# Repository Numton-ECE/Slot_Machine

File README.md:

Analog Slot Machine – 3-Digit Random Number Generator
=====================================================

This project is a fully discrete, CMOS-based 3-digit “slot machine” random number
generator designed in KiCad. A transistor noise source, analog amplification, and a
comparator generate a pseudo-random clock that drives three CD4026 decade counters and
7-segment LED displays. There is no microcontroller involved.

In normal use:
- A 2N3904 transistor is biased so it produces broadband electronic noise.
- An LM358 dual op-amp amplifies that noise and also creates a mid-supply reference (V_REF).
- An LM393 comparator compares the noisy signal to V_REF and outputs a pseudo-random
  digital clock (CLK).
- CD4013 flip-flops and a CD4081 AND gate handle the RUN state and decide when CLK is
  allowed through.
- Three CD4026 counters drive three 7-segment LED displays (e.g. 5161AS), forming a
  3-digit readout.
- When you hold the RUN pushbutton, the digits “spin”; when you release it, the
  current 3-digit number is frozen on the display.
- The whole circuit runs from a single 9 V battery (PP3).

Hardware Architecture
---------------------

1) Power and Decoupling
- Input is a 9 V battery, with VDD and GND as the main rails.
- Each IC has a 100 nF ceramic capacitor close to its power pins to keep the supply
  clean at high frequencies.
- Electrolytic capacitors on the 9 V rail provide bulk smoothing and help with
  startup and transients.
- This keeps both the analog and digital blocks stable and less sensitive to noise.

2) Noise and Clock Generation
- A 2N3904 NPN transistor is biased in a regime where it naturally produces broadband
  electronic noise. High-value resistors and a small capacitor shape this noise a bit.
- The LM358 op-amp does two jobs:
  - One channel generates V_REF, roughly at mid-supply.
  - The other channel amplifies and band-limits the noise so the comparator sees a
    clean, usable signal.
- The LM393 comparator compares the amplified noise to V_REF:
  - Whenever the noise crosses the reference, the comparator output toggles.
  - This produces a jittery, pseudo-random digital clock signal (CLK), which becomes
    the timing source for the counters.

3) Run / Sync Control and Clock Gating
- A CD4013 dual D-type flip-flop stores the RUN state and any related control bits.
- A dual-pole momentary RUN pushbutton, along with a few diodes and resistors,
  generates clean set/reset and edge-detect pulses so the flip-flop behaves nicely.
- A CD4081 quad 2-input AND gate combines:
  - The random clock (CLK),
  - The RUN state,
  - And any extra gating signals used per digit.
- When RUN is active, CLK passes through the AND gates and reaches the CD4026 counters.
- When RUN is inactive, the clock path is cut off and the counters simply hold their
  last values.
- An SPDT switch is available to select between different modes (for example,
  changing how reset or test behavior works), depending on how you choose to wire it.

4) Counters and Display
- Three CD4026 decade counters are used, one for each decimal digit:
  - Each counter receives a gated clock input from the CD4081, plus reset and control
    wiring for predictable startup.
  - CD4026 devices include built-in 7-segment decoding, so no extra decoder IC is needed.
- Three 7-segment LED displays (such as 5161AS) are driven directly from the CD4026
  outputs through current-limiting resistors (about 2.2 kΩ per segment).
- Together they form a simple 3-digit decimal display:
  - While you hold RUN, the digits advance quickly and look like spinning reels.
  - When you release RUN, the clock stops and the last 3-digit number stays on the
    display until the next run.

Usage
-----

- Open the KiCad project to inspect the schematic and PCB layout.
- If you want a physical board, generate Gerber and drill files from the KiCad PCB
  and send them to a PCB manufacturer.
- Assemble the board starting with resistors and capacitors, then sockets and
  connectors, and finally the ICs and displays.
- After soldering, check that the power rails are correct and there are no shorts
  between VDD and GND.
- Connect a 9 V battery.
- Press and hold the RUN button: the digits should spin rapidly.
- Release RUN: a random 3-digit number should remain displayed.

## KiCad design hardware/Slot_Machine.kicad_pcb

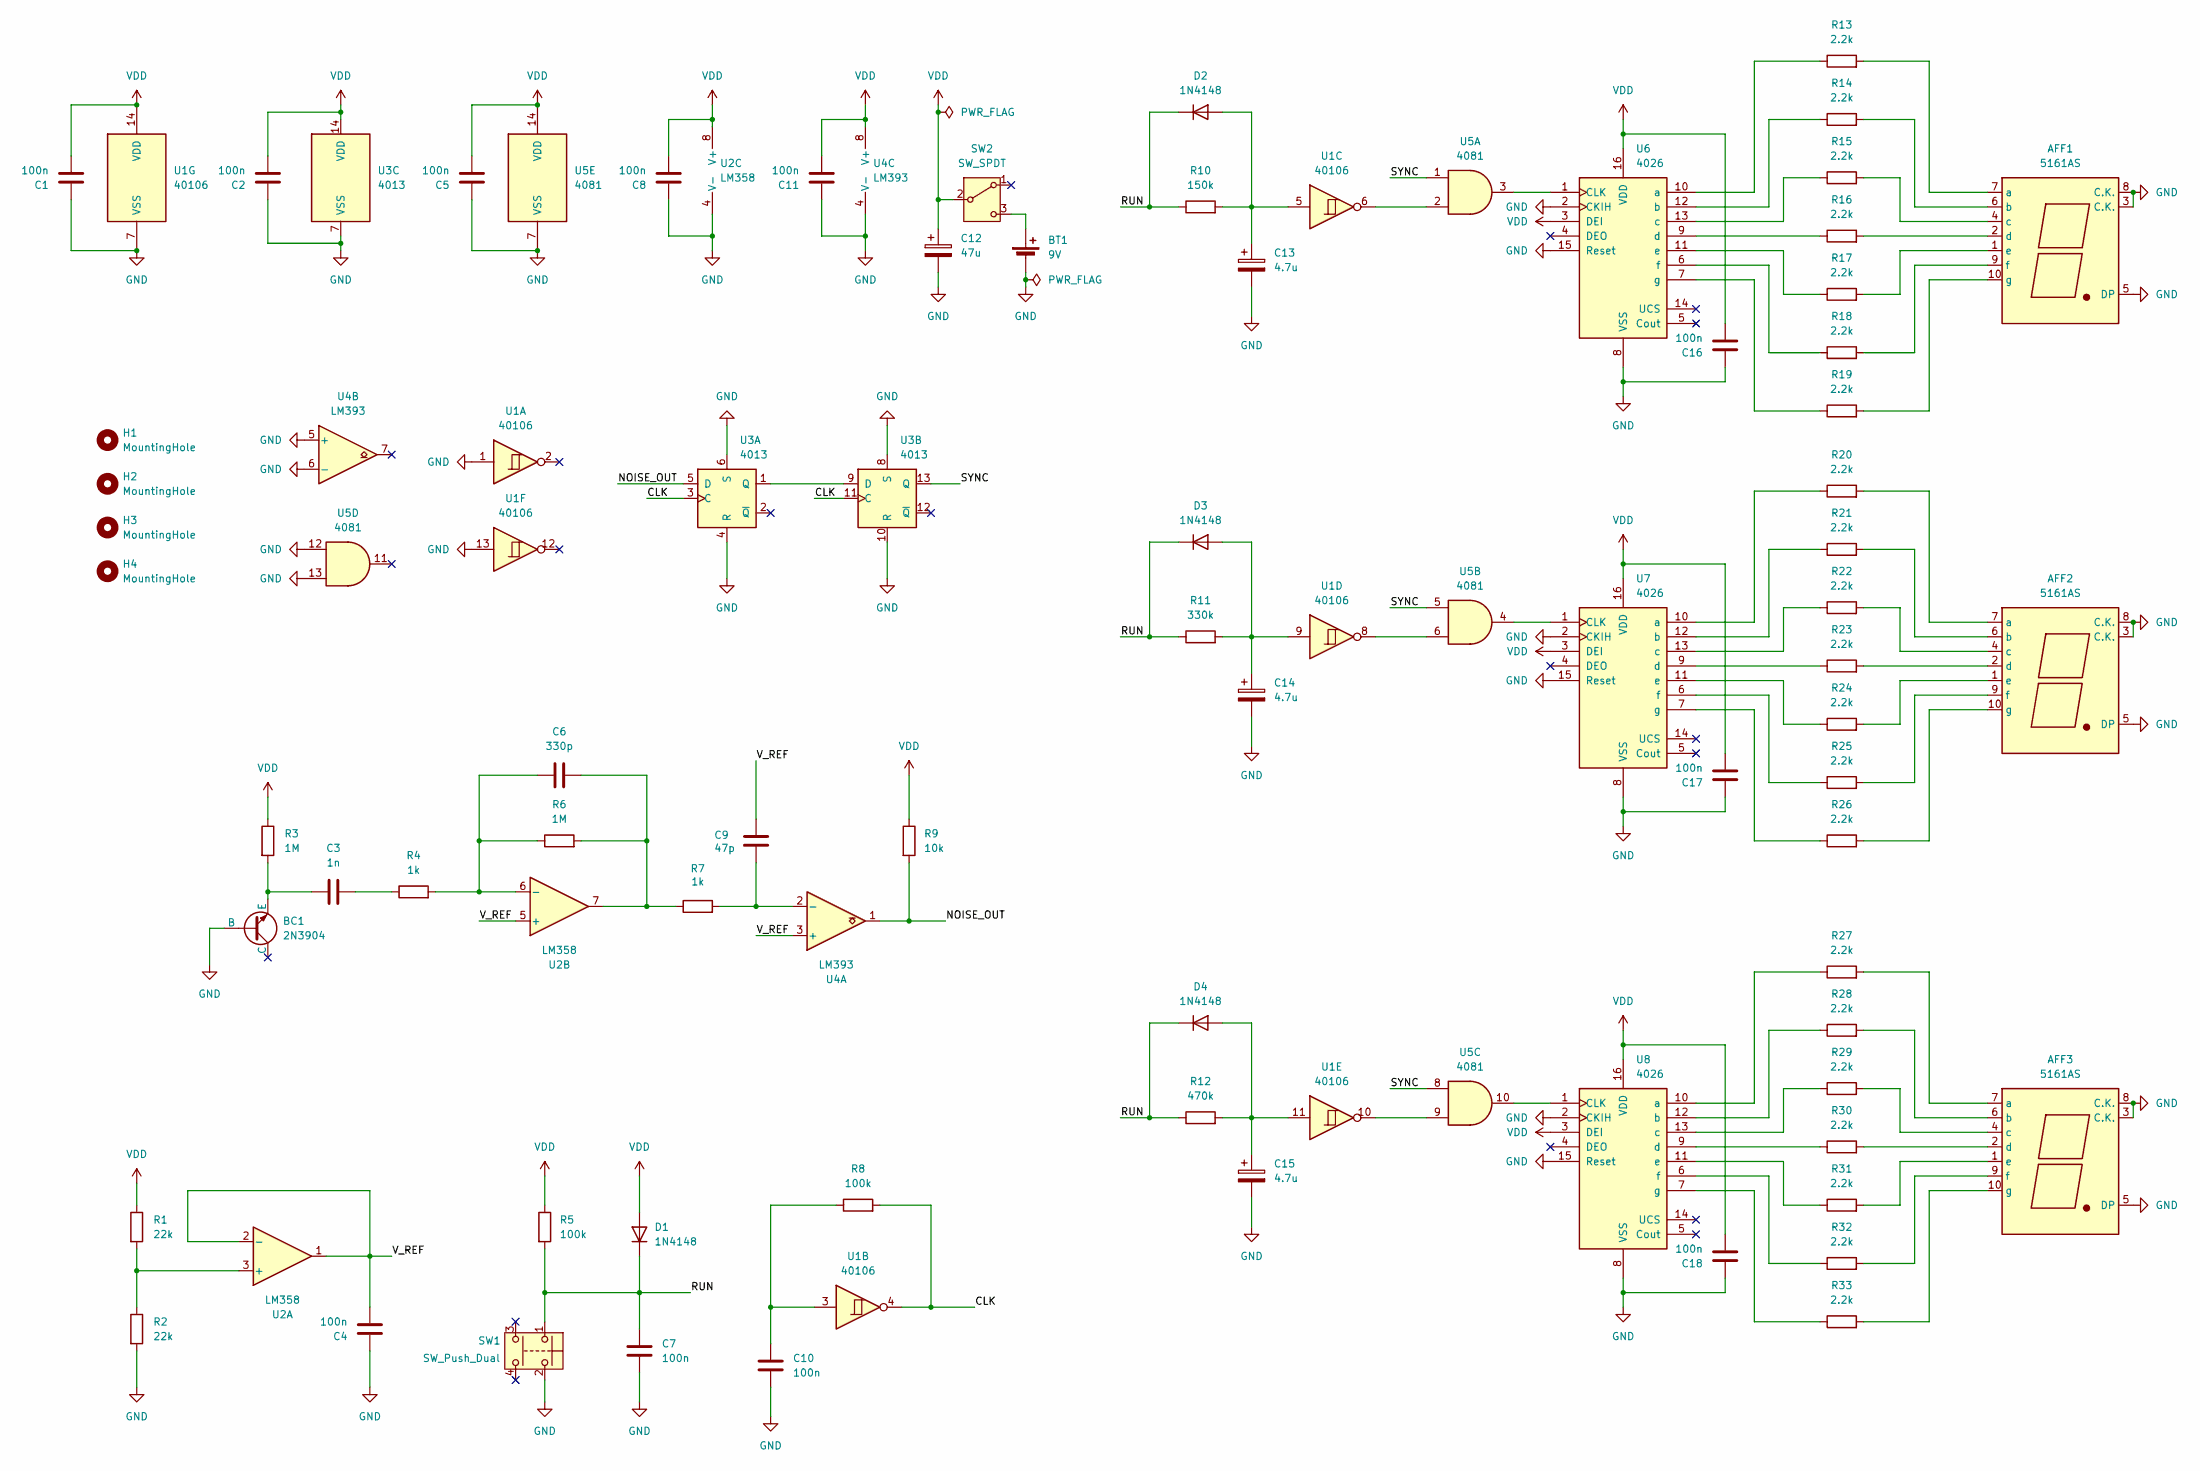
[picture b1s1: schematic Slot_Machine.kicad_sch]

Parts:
AFF1, AFF2, AFF3: 5161AS; 7SegmentLED_LTS6760_LTS6780
BC1: 2N3904; TO-92_Inline
BT1: 9V; BatteryHolder_MPD_BA9VPC_1xPP3
C1, C2, C4, C5, C7, C8, C10, C11, C16, C17, C18: 100n; C_Disc_D5.0mm_W2.5mm_P5.00mm
C3: 1n; C_Disc_D5.0mm_W2.5mm_P5.00mm
C6: 330p; C_Disc_D5.0mm_W2.5mm_P5.00mm
C9: 47p; C_Disc_D5.0mm_W2.5mm_P5.00mm
C12: 47u; CP_Radial_D6.3mm_P2.50mm
C13, C14, C15: 4.7u; CP_Radial_D5.0mm_P2.50mm
D1, D2, D3, D4: 1N4148; D_DO-35_SOD27_P7.62mm_Horizontal
H1, H2, H3, H4: MountingHole; MountingHole_3.2mm_M3
R1, R2: 22k; R_Axial_DIN0207_L6.3mm_D2.5mm_P7.62mm_Horizontal
R3, R6: 1M; R_Axial_DIN0207_L6.3mm_D2.5mm_P7.62mm_Horizontal
R4, R7: 1k; R_Axial_DIN0207_L6.3mm_D2.5mm_P7.62mm_Horizontal
R5, R8: 100k; R_Axial_DIN0207_L6.3mm_D2.5mm_P7.62mm_Horizontal
R9: 10k; R_Axial_DIN0207_L6.3mm_D2.5mm_P7.62mm_Horizontal
R10: 150k; R_Axial_DIN0207_L6.3mm_D2.5mm_P7.62mm_Horizontal
R11: 330k; R_Axial_DIN0207_L6.3mm_D2.5mm_P7.62mm_Horizontal
R12: 470k; R_Axial_DIN0207_L6.3mm_D2.5mm_P7.62mm_Horizontal
R13, R14, R15, R16, R17, R18, R19, R20, R21, R22, R23, R24, R25, R26, R27, R28, R29, R30, R31, R32, R33: 2.2k; R_Axial_DIN0207_L6.3mm_D2.5mm_P7.62mm_Horizontal
SW1: SW_Push_Dual; SW_Push_2P1T_Toggle_CK_PVA1xxH4xxxxxxV2
SW2: SW_SPDT; SW_Slide-03_Wuerth-WS-SLTV_10x2.5x6.4_P2.54mm_Custom
U1: 40106; DIP-14_W7.62mm
U2: LM358; DIP-8_W7.62mm
U3: 4013; DIP-14_W7.62mm
U4: LM393; DIP-8_W7.62mm
U5: 4081; DIP-14_W7.62mm
U6, U7, U8: 4026; DIP-16_W7.62mm

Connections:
/CLK: R8.2, U1.4, U3.3 (C), U3.11 (C)
/NOISE_OUT: R9.2, U3.5 (D), U4.1
/RUN: C7.1, D1.1 (K), D2.1 (K), D3.1 (K), D4.1 (K), R5.2, R10.1, R11.1, R12.1, SW1.1
/SYNC: U3.13 (Q), U5.1, U5.5, U5.8
/V_REF: C4.2, C9.1, U2.1, U2.2 (-), U2.5 (+), U4.3 (+)
GND: AFF1.3 (C.K.), AFF1.5 (DP), AFF1.8 (C.K.), AFF2.3 (C.K.), AFF2.5 (DP), AFF2.8 (C.K.), AFF3.3 (C.K.), AFF3.5 (DP), AFF3.8 (C.K.), BC1.2 (B), BT1.2 (-), C1.1, C2.1, C4.1, C5.1, C7.2, C8.1, C10.2, C11.1, C12.2, C13.2, C14.2, C15.2, C16.1, C17.1, C18.1, R2.2, SW1.2, U1.1, U1.7 (VSS), U1.13, U2.4 (V-), U3.4 (R), U3.6 (S), U3.7 (VSS), U3.8 (S), U3.10 (R), U4.4 (V-), U4.5 (+), U4.6 (-), U5.7 (VSS), U5.12, U5.13, U6.2 (CKIH), U6.8 (VSS), U6.15 (Reset), U7.2 (CKIH), U7.8 (VSS), U7.15 (Reset), U8.2 (CKIH), U8.8 (VSS), U8.15 (Reset)
unnamed: AFF1.7 (a), R13.2
unnamed: AFF1.6 (b), R14.2
unnamed: AFF1.4 (c), R15.2
unnamed: AFF1.2 (d), R16.2
unnamed: AFF1.1 (e), R17.2
unnamed: AFF1.9 (f), R18.2
unnamed: AFF1.10 (g), R19.2
unnamed: AFF2.7 (a), R20.2
unnamed: AFF2.6 (b), R21.2
unnamed: AFF2.4 (c), R22.2
unnamed: AFF2.2 (d), R23.2
unnamed: AFF2.1 (e), R24.2
unnamed: AFF2.9 (f), R25.2
unnamed: AFF2.10 (g), R26.2
unnamed: AFF3.7 (a), R27.2
unnamed: AFF3.6 (b), R28.2
unnamed: AFF3.4 (c), R29.2
unnamed: AFF3.2 (d), R30.2
unnamed: AFF3.1 (e), R31.2
unnamed: AFF3.9 (f), R32.2
unnamed: AFF3.10 (g), R33.2
unnamed: BC1.3 (E), C3.1, R3.2
unnamed: BT1.1 (+), SW2.3 (C)
unnamed: C3.2, R4.1
unnamed: C6.2, R6.2, R7.1, U2.7
unnamed: C10.1, R8.1, U1.3
unnamed: C13.1, D2.2 (A), R10.2, U1.5
unnamed: C14.1, D3.2 (A), R11.2, U1.9
unnamed: C15.1, D4.2 (A), R12.2, U1.11
unnamed: U1.6, U5.2
unnamed: U1.8, U5.6
unnamed: U1.10, U5.9
unnamed: R1.2, R2.1, U2.3 (+)
unnamed: C6.1, R4.2, R6.1, U2.6 (-)
unnamed: U3.1 (Q), U3.9 (D)
unnamed: C9.2, R7.2, U4.2 (-)
unnamed: U5.3, U6.1 (CLK)
unnamed: R13.1, U6.10 (a)
unnamed: R14.1, U6.12 (b)
unnamed: R15.1, U6.13 (c)
unnamed: R16.1, U6.9 (d)
unnamed: R17.1, U6.11 (e)
unnamed: R18.1, U6.6 (f)
unnamed: R19.1, U6.7 (g)
unnamed: U5.4, U7.1 (CLK)
unnamed: R20.1, U7.10 (a)
unnamed: R21.1, U7.12 (b)
unnamed: R22.1, U7.13 (c)
unnamed: R23.1, U7.9 (d)
unnamed: R24.1, U7.11 (e)
unnamed: R25.1, U7.6 (f)
unnamed: R26.1, U7.7 (g)
unnamed: U5.10, U8.1 (CLK)
unnamed: R27.1, U8.10 (a)
unnamed: R28.1, U8.12 (b)
unnamed: R29.1, U8.13 (c)
unnamed: R30.1, U8.9 (d)
unnamed: R31.1, U8.11 (e)
unnamed: R32.1, U8.6 (f)
unnamed: R33.1, U8.7 (g)
VDD: C1.2, C2.2, C5.2, C8.2, C11.2, C12.1, C16.2, C17.2, C18.2, D1.2 (A), R1.1, R3.1, R5.1, R9.1, SW2.2 (B), U1.14 (VDD), U2.8 (V+), U3.14 (VDD), U4.8 (V+), U5.14 (VDD), U6.3 (DEI), U6.16 (VDD), U7.3 (DEI), U7.16 (VDD), U8.3 (DEI), U8.16 (VDD)

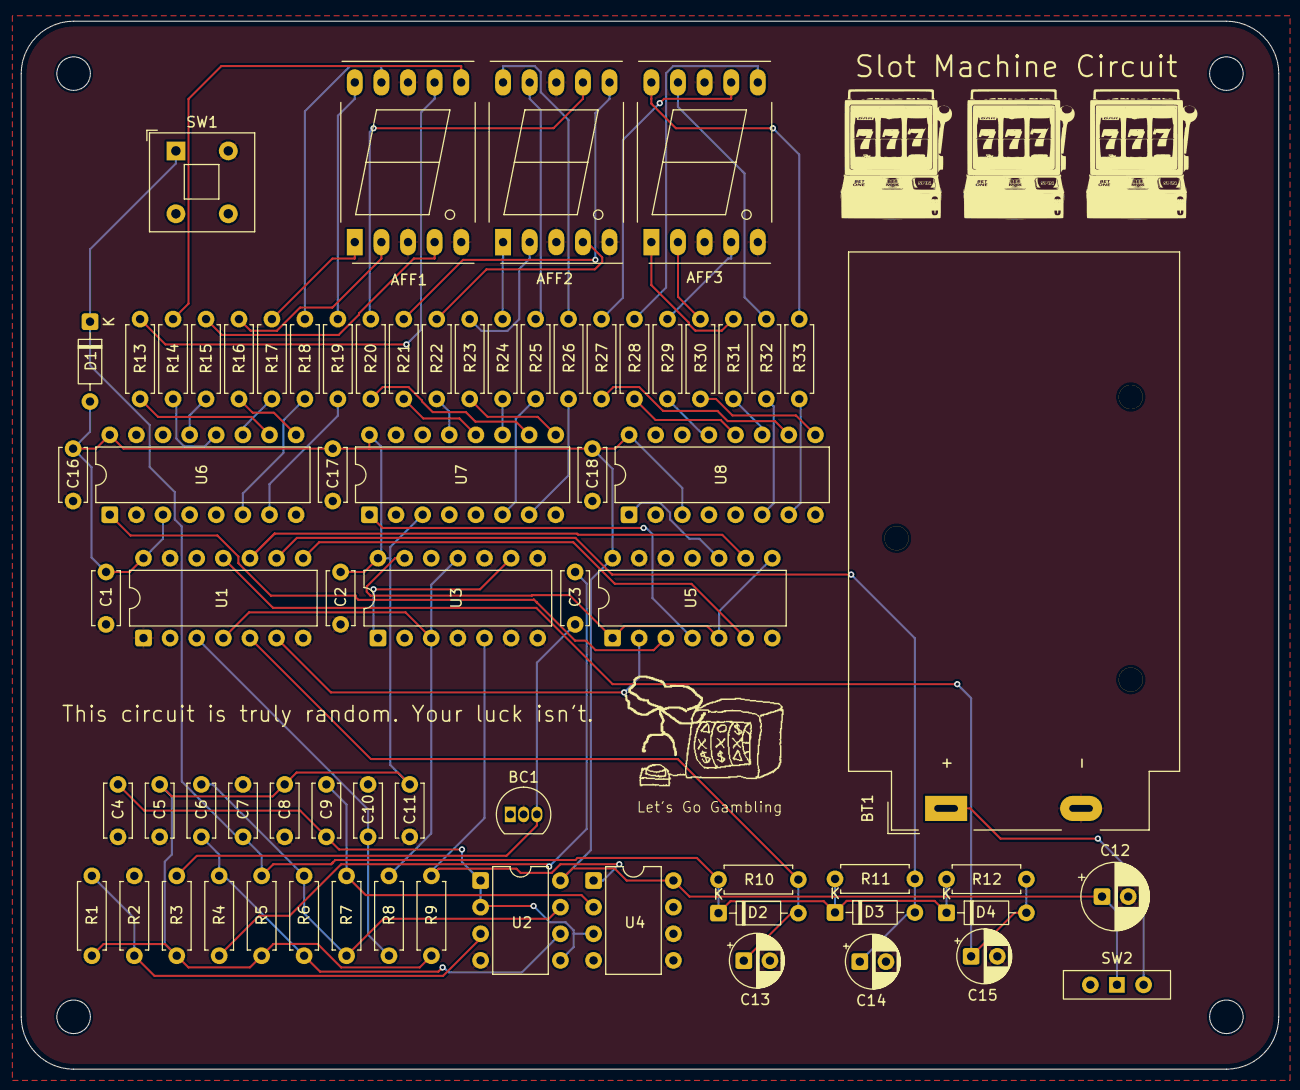
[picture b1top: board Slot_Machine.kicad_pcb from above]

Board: 2 copper layers, 120.0 x 100.0 mm, 79 parts (1 on the bottom side), 67 nets.

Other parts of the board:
G1, G2, G3, G4, G5: LOGO

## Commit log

2025-12-02 Describe what you changed here
2025-12-02 Added 3D Views
2025-12-03 Change component values and add files
2025-12-03 Change README
